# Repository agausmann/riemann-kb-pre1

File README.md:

# Riemann

A pseudo-split 60% ortholinear keyboard.

## Main Features

- 60 keys in a 5x12 grid

- Supports MX-style switches

- Per-key RGB

- Hot-swappable

- QMK support (TODO)

## Design

- Designed with the features that I want, with no compromises.

- Designed to be factory-assembled, _not_ hand-soldered (I want to be able to rely on this, and I don't trust my soldering skills _that_ much).

- Microcontroller is selected to be compatible with the [Rust] programming 
language (unfortunately it does not have good support for AVR)

- PRETTY COLORS (RGB LEDs are based on the APA102 IC for that sweet, sweet
dynamic range, compared to WS2812)

[Rust]: https://rust-lang.org

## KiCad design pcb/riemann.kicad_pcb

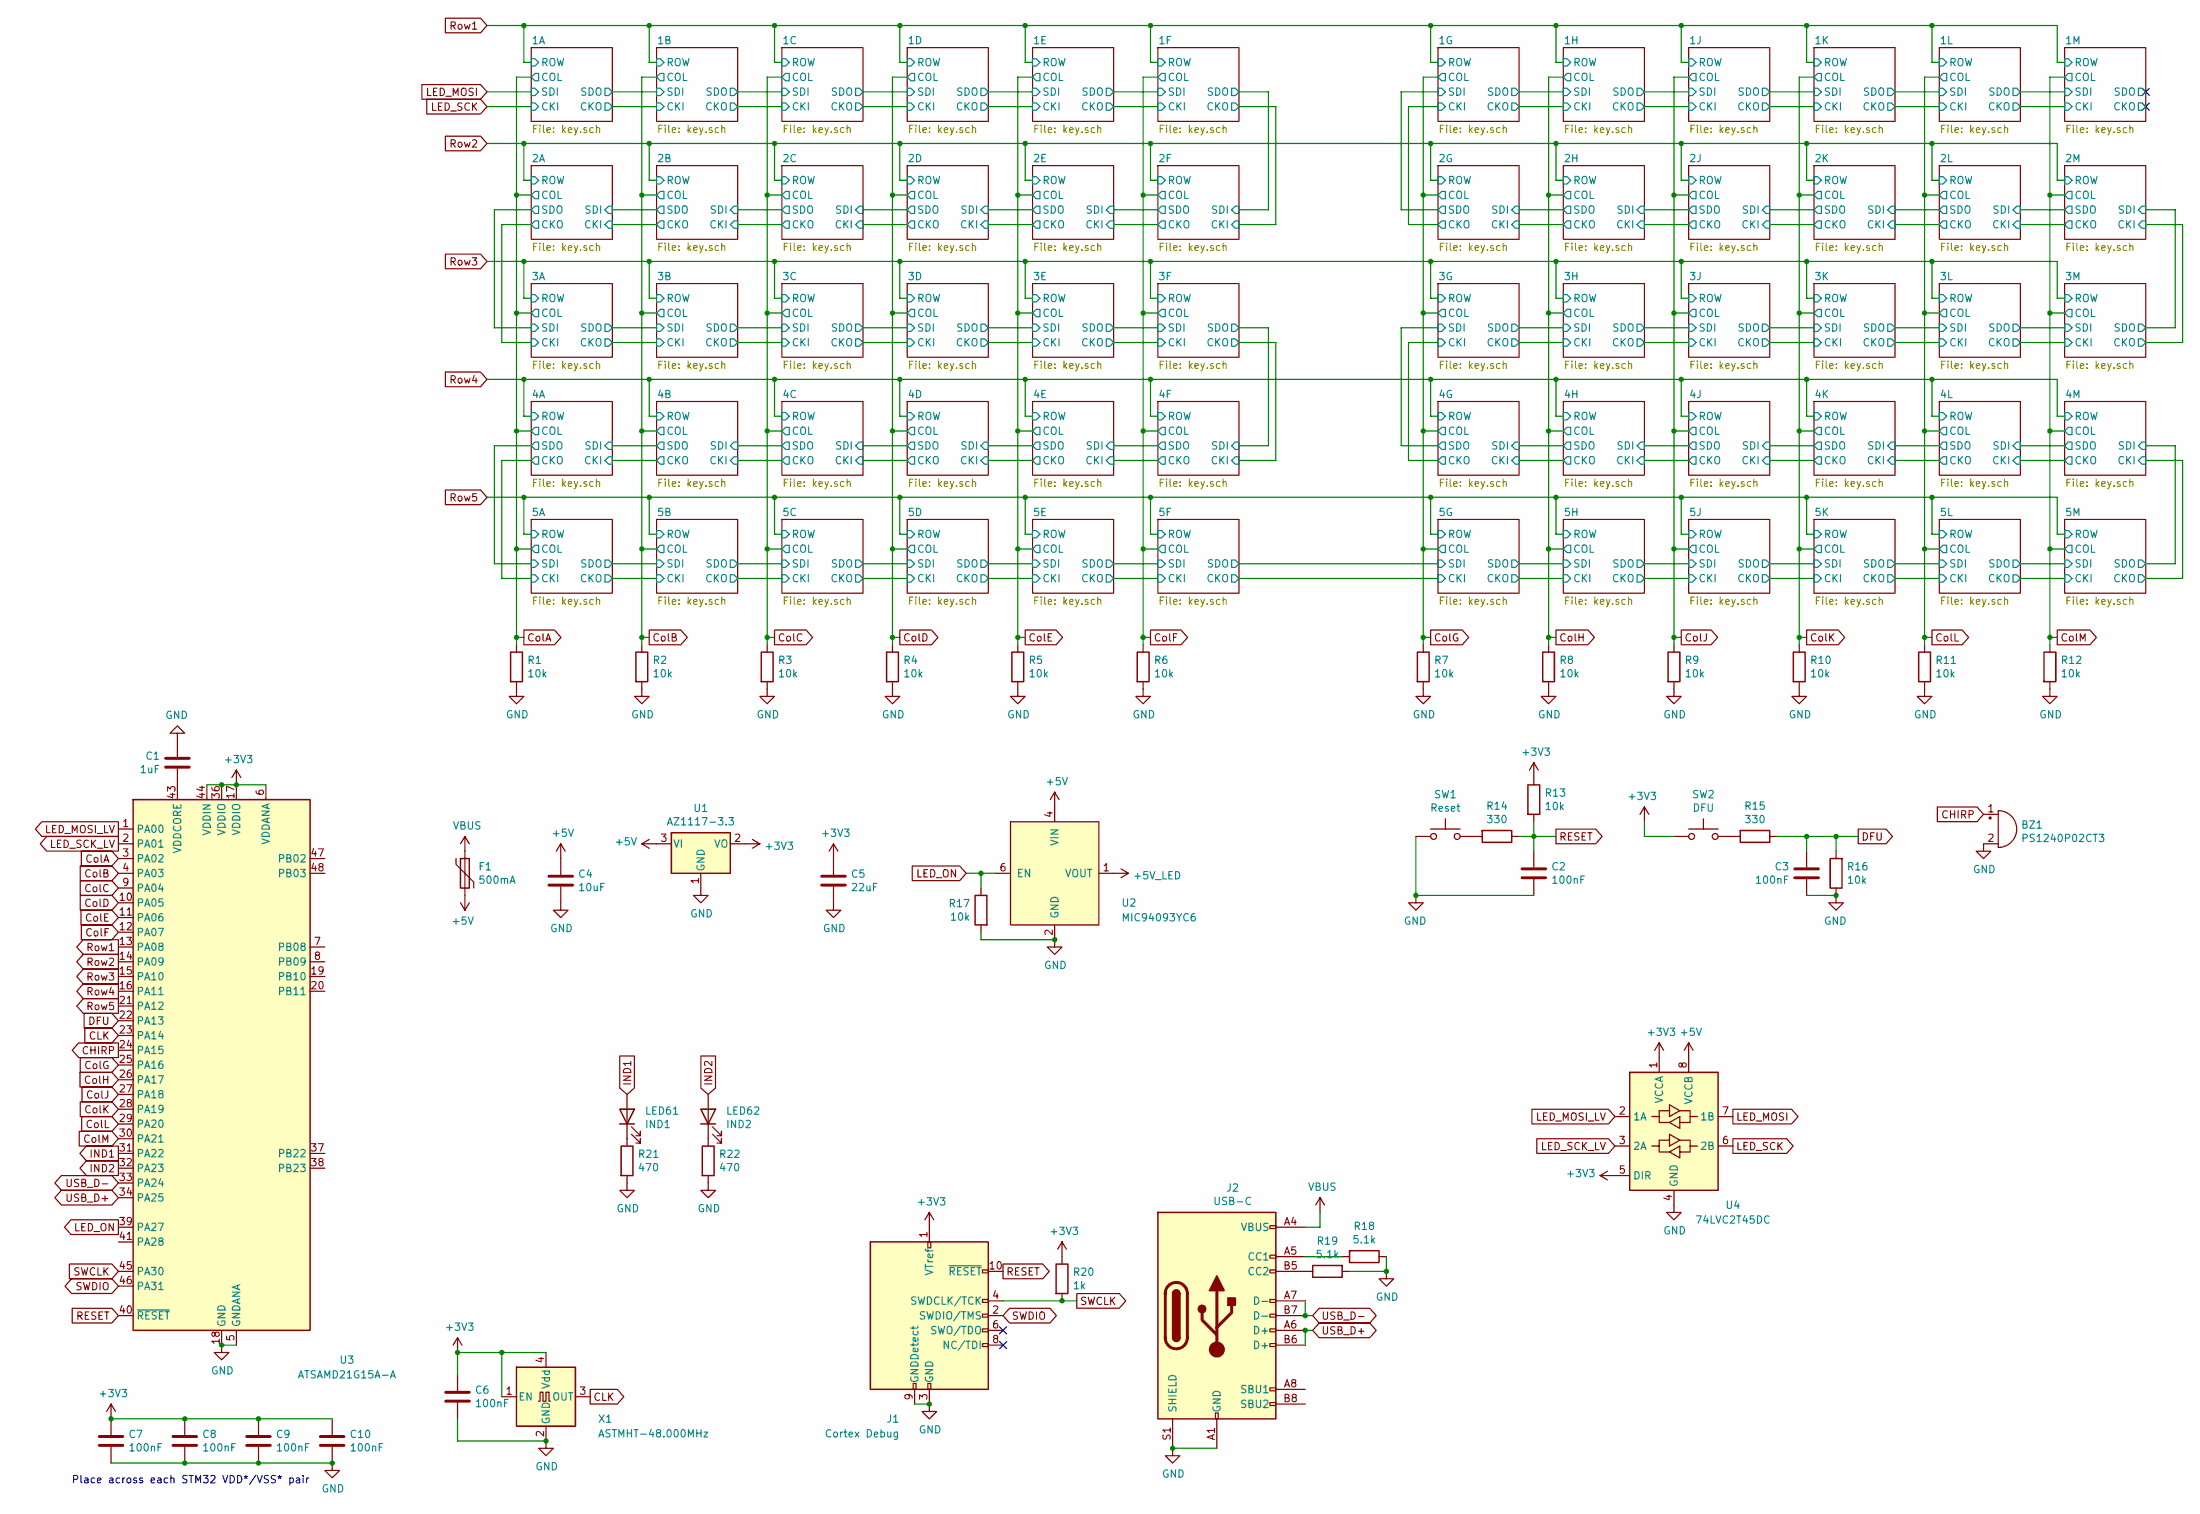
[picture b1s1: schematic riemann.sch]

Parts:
BZ1: PS1240P02CT3; Buzzer_TDK_PS1240P02BT_D12.2mm_H6.5mm; Mfr. Part PS1240P02CT3; Digikey 445-5229-1-ND
C1: 1uF; C_0402_1005Metric; Mfr. Part CL05A105MQ5NNNC; Digikey 1276-1235-1-ND
C2, C3: 100nF; C_0603_1608Metric; Mfr. Part CL10B104KA8NNNC; Digikey 1276-1006-1-ND
C4: 10uF; C_0805_2012Metric; Mfr. Part CL21A106KOFNNNE; Digikey 1276-2893-1-ND
C5: 22uF; C_0805_2012Metric; Mfr. Part CL21A226MOCLRNC; Digikey 1276-6780-1-ND
C6, C7, C8, C9, C10: 100nF; C_0402_1005Metric; Mfr. Part CL05A104KA5NNNC; Digikey 1276-1043-1-ND
F1: 500mA; Fuse_0805_2012Metric_Castellated; Mfr. Part 0ZCK0050FF2E; Digikey 507-1813-1-ND
J1: Cortex Debug; Samtec_FTSH-105_2x05_P1.27mm_Keyed_Vertical; Mfr. Part FTSH-105-01-L-DV-K-A-P-TR; Digikey SAM13163CT-ND
J2: USB-C; USB_C_Receptacle_GCT_USB4105; Mfr. Part USB4105-GF-A; Digikey 2073-USB4105-GF-ACT-ND
LED61: IND1; LED_0603_1608Metric; Mfr. Part 150060AS75000; Digikey 732-150060AS75000CT-ND
LED62: IND2; LED_0603_1608Metric; Mfr. Part 150060BS75000; Digikey 732-4966-1-ND
R1, R2, R3, R4, R5, R6, R7, R8, R9, R10, R11, R12, R13, R16, R17: 10k; R_0603_1608Metric; Mfr. Part RMCF0603FT10K0; Digikey RMCF0603FT10K0CT-ND
R14, R15: 330; R_0603_1608Metric; Mfr. Part RMCF0603FT330R; Digikey RMCF0603FT330RCT-ND
R18, R19: 5.1k; R_0603_1608Metric; Mfr. Part RMCF0603FT5K10; Digikey RMCF0603FT5K10CT-ND
R20: 1k; R_0402_1005Metric; Mfr. Part RMCF0402FT1K00; Digikey RMCF0402FT1K00CT-ND
R21, R22: 470; R_0603_1608Metric
SW1: Reset; SW_Push_1P1T_NO_6x6mm_H9.5mm; Mfr. Part PTS645SL43SMTR92 LFS; Digikey CKN10880CT-ND
SW2: DFU; SW_Push_1P1T_NO_6x6mm_H9.5mm; Mfr. Part PTS645SL43SMTR92 LFS; Digikey CKN10880CT-ND
U1: AZ1117-3.3; SOT-223-3_TabPin2; Mfr. Part AZ1117IH-3.3TRG1; Digikey AZ1117IH-3.3TRG1DICT-ND
U2: MIC94093YC6; SOT-363_SC-70-6; Mfr. Part MIC94093YC6-TR; Digikey 576-3490-1-ND
U3: ATSAMD21G15A-A; TQFP-48_7x7mm_P0.5mm; Mfr. Part ATSAMD21G18A-AFT; Digikey ATSAMD21G18A-AFTCT-ND
U4: 74LVC2T45DC; VSSOP-8_2.3x2mm_P0.5mm; Mfr. Part 74LVCH2T45DC,125; Digikey 1727-4596-1-ND
X1: ASTMHT-48.000MHz; Oscillator_SMD_Abracon_ASE-4Pin_3.2x2.5mm; Mfr. Part ASTMHTE-48.000MHZ-AJ-E-T; Digikey 535-13269-1-ND

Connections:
+3V3: C5.1, C6.1, C7.1, C8.1, C9.1, C10.1, J1.1 (VTref), R13.1, R20.1, SW2.2, U1.2 (VO), U3.6 (VDDANA), U3.17 (VDDIO), U3.36 (VDDIO), U3.44 (VDDIN), U4.1 (VCCA), U4.5 (DIR), X1.1 (EN), X1.4 (Vdd)
+5V: C4.1, F1.2, U1.3 (VI), U2.4 (VIN), U4.8 (VCCB)
+5V_LED: U2.1 (VOUT); also elsewhere on the board
CHIRP: BZ1.1 (-), U3.24 (PA15)
CLK: U3.23 (PA14), X1.3 (OUT)
ColA: R1.1, U3.3 (PA02); also elsewhere on the board
ColB: R2.1, U3.4 (PA03); also elsewhere on the board
ColC: R3.1, U3.9 (PA04); also elsewhere on the board
ColD: R4.1, U3.10 (PA05); also elsewhere on the board
ColE: R5.1, U3.11 (PA06); also elsewhere on the board
ColF: R6.1, U3.12 (PA07); also elsewhere on the board
ColG: R7.1, U3.25 (PA16); also elsewhere on the board
ColH: R8.1, U3.26 (PA17); also elsewhere on the board
ColJ: R9.1, U3.27 (PA18); also elsewhere on the board
ColK: R10.1, U3.28 (PA19); also elsewhere on the board
ColL: R11.1, U3.29 (PA20); also elsewhere on the board
ColM: R12.1, U3.30 (PA21); also elsewhere on the board
DFU: C3.1, R15.1, R16.2, U3.22 (PA13)
GND: BZ1.2 (+), C1.2, C2.2, C3.2, C4.2, C5.2, C6.2, C7.2, C8.2, C9.2, C10.2, J1.3 (GND), J1.5 (GND), J1.9 (GNDDetect), J2.A1 (GND), J2.A12 (GND), J2.B1 (GND), J2.B12 (GND), J2.S1 (SHIELD), R1.2, R2.2, R3.2, R4.2, R5.2, R6.2, R7.2, R8.2, R9.2, R10.2, R11.2, R12.2, R16.1, R17.2, R18.1, R19.2, R21.2, R22.2, SW1.1, U1.1 (GND), U2.2 (GND), U2.5 (GND), U3.5 (GNDANA), U3.18 (GND), U3.35 (GND), U3.42 (GND), U4.4 (GND), X1.2 (GND); also elsewhere on the board
IND1: LED61.2 (A), U3.31 (PA22)
IND2: LED62.2 (A), U3.32 (PA23)
LED_MOSI: U4.7 (1B); also elsewhere on the board
LED_MOSI_LV: U3.1 (PA00), U4.2 (1A)
LED_ON: R17.1, U2.6 (EN), U3.39 (PA27)
LED_SCK: U4.6 (2B); also elsewhere on the board
LED_SCK_LV: U3.2 (PA01), U4.3 (2A)
unnamed: C1.1, U3.43 (VDDCORE)
unnamed: J2.A5 (CC1), R18.2
unnamed: J2.B5 (CC2), R19.1
unnamed: LED61.1 (K), R21.1
unnamed: LED62.1 (K), R22.1
unnamed: R14.2, SW1.2
unnamed: R15.2, SW2.1
RESET: C2.1, J1.10 (~RESET~), R13.2, R14.1, U3.40 (~RESET)
Row1: U3.13 (PA08); also elsewhere on the board
Row2: U3.14 (PA09); also elsewhere on the board
Row3: U3.15 (PA10); also elsewhere on the board
Row4: U3.16 (PA11); also elsewhere on the board
Row5: U3.21 (PA12); also elsewhere on the board
SWCLK: J1.4 (SWDCLK/TCK), R20.2, U3.45 (PA30)
SWDIO: J1.2 (SWDIO/TMS), U3.46 (PA31)
USB_D+: J2.A6 (D+), J2.B6 (D+), U3.34 (PA25)
USB_D-: J2.A7 (D-), J2.B7 (D-), U3.33 (PA24)
VBUS: F1.1, J2.A4 (VBUS), J2.A9 (VBUS), J2.B4 (VBUS), J2.B9 (VBUS)

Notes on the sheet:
Place across each STM32 VDD*/VSS* pair

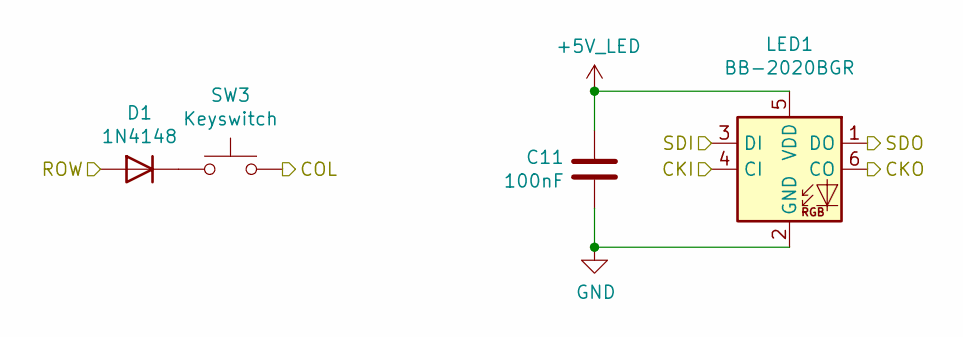
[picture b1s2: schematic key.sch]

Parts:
C11: 100nF; C_0402_1005Metric; Mfr. Part CL05A104KA5NNNC; Digikey 1276-1043-1-ND
D1: 1N4148; D_SOD-123; Mfr. Part 1N4148WSTR; Digikey 1655-1359-1-ND
LED1: BB-2020BGR; LED-BB-2020BGR; Mfr. Part BB-2020BGR-TRB; Digikey 2007-BB-2020BGR-TRBCT-ND
SW3: Keyswitch; SW_GateronRGB_KailhSocket_1.00u_PCB; Mfr. Part CPG151101S11

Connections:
+5V_LED: C11.2, LED1.5 (VDD); also elsewhere on the board
/1B/CKI: LED1.6 (CO); also elsewhere on the board
/1B/SDI: LED1.1 (DO); also elsewhere on the board
ColA: SW3.2; also elsewhere on the board
GND: C11.1, LED1.2 (GND); also elsewhere on the board
LED_MOSI: LED1.3 (DI); also elsewhere on the board
LED_SCK: LED1.4 (CI); also elsewhere on the board
unnamed: D1.1 (K), SW3.1
Row1: D1.2 (A); also elsewhere on the board

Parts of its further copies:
C12, C13, C14, C15, C16, C17, C18, C19, C20, C21, C22, C23, C24, C25, C26, C27, C28, C29, C30, C31, C32, C33, C34, C35, C36, C37, C38, C39, C40, C41, C42, C43, C44, C45, C46, C47, C48, C49, C50, C51, C52, C53, C54, C55, C56, C57, C58, C59, C60, C61, C62, C63, C64, C65, C66, C67, C68, C69, C70: 100nF; C_0402_1005Metric; Mfr. Part CL05A104KA5NNNC; Digikey 1276-1043-1-ND
D2, D3, D4, D5, D6, D7, D8, D9, D10, D11, D12, D13, D14, D15, D16, D17, D18, D19, D20, D21, D22, D23, D24, D25, D26, D27, D28, D29, D30, D31, D32, D33, D34, D35, D36, D37, D38, D39, D40, D41, D42, D43, D44, D45, D46, D47, D48, D49, D50, D51, D52, D53, D54, D55, D56, D57, D58, D59, D60: 1N4148; D_SOD-123; Mfr. Part 1N4148WSTR; Digikey 1655-1359-1-ND
LED2, LED3, LED4, LED5, LED6, LED7, LED8, LED9, LED10, LED11, LED12, LED13, LED14, LED15, LED16, LED17, LED18, LED19, LED20, LED21, LED22, LED23, LED24, LED25, LED26, LED27, LED28, LED29, LED30, LED31, LED32, LED33, LED34, LED35, LED36, LED37, LED38, LED39, LED40, LED41, LED42, LED43, LED44, LED45, LED46, LED47, LED48, LED49, LED50, LED51, LED52, LED53, LED54, LED55, LED56, LED57, LED58, LED59, LED60: BB-2020BGR; LED-BB-2020BGR; Mfr. Part BB-2020BGR-TRB; Digikey 2007-BB-2020BGR-TRBCT-ND
SW4, SW5, SW6, SW7, SW8, SW9, SW10, SW11, SW12, SW13, SW14, SW15, SW16, SW17, SW18, SW19, SW20, SW21, SW22, SW23, SW24, SW25, SW26, SW27, SW28, SW29, SW30, SW31, SW32, SW33, SW34, SW35, SW36, SW37, SW38, SW39, SW40, SW41, SW42, SW43, SW44, SW45, SW46, SW47, SW48, SW49, SW50, SW51, SW52, SW53, SW54, SW55, SW56, SW57, SW58, SW59, SW60, SW61, SW62: Keyswitch; SW_GateronRGB_KailhSocket_1.00u_PCB; Mfr. Part CPG151101S11

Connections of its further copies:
+5V_LED: C12.2, C13.2, C14.2, C15.2, C16.2, C17.2, C18.2, C19.2, C20.2, C21.2, C22.2, C23.2, C24.2, C25.2, C26.2, C27.2, C28.2, C29.2, C30.2, C31.2, C32.2, C33.2, C34.2, C35.2, C36.2, C37.2, C38.2, C39.2, C40.2, C41.2, C42.2, C43.2, C44.2, C45.2, C46.2, C47.2, C48.2, C49.2, C50.2, C51.2, C52.2, C53.2, C54.2, C55.2, C56.2, C57.2, C58.2, C59.2, C60.2, C61.2, C62.2, C63.2, C64.2, C65.2, C66.2, C67.2, C68.2, C69.2, C70.2, LED2.5 (VDD), LED3.5 (VDD), LED4.5 (VDD), LED5.5 (VDD), LED6.5 (VDD), LED7.5 (VDD), LED8.5 (VDD), LED9.5 (VDD), LED10.5 (VDD), LED11.5 (VDD), LED12.5 (VDD), LED13.5 (VDD), LED14.5 (VDD), LED15.5 (VDD), LED16.5 (VDD), LED17.5 (VDD), LED18.5 (VDD), LED19.5 (VDD), LED20.5 (VDD), LED21.5 (VDD), LED22.5 (VDD), LED23.5 (VDD), LED24.5 (VDD), LED25.5 (VDD), LED26.5 (VDD), LED27.5 (VDD), LED28.5 (VDD), LED29.5 (VDD), LED30.5 (VDD), LED31.5 (VDD), LED32.5 (VDD), LED33.5 (VDD), LED34.5 (VDD), LED35.5 (VDD), LED36.5 (VDD), LED37.5 (VDD), LED38.5 (VDD), LED39.5 (VDD), LED40.5 (VDD), LED41.5 (VDD), LED42.5 (VDD), LED43.5 (VDD), LED44.5 (VDD), LED45.5 (VDD), LED46.5 (VDD), LED47.5 (VDD), LED48.5 (VDD), LED49.5 (VDD), LED50.5 (VDD), LED51.5 (VDD), LED52.5 (VDD), LED53.5 (VDD), LED54.5 (VDD), LED55.5 (VDD), LED56.5 (VDD), LED57.5 (VDD), LED58.5 (VDD), LED59.5 (VDD), LED60.5 (VDD); also elsewhere on the board
/1B/CKI: LED2.4 (CI); also elsewhere on the board
/1B/SDI: LED2.3 (DI); also elsewhere on the board
/1C/CKI: LED2.6 (CO), LED3.4 (CI)
/1C/SDI: LED2.1 (DO), LED3.3 (DI)
/1D/CKI: LED3.6 (CO), LED4.4 (CI)
/1D/SDI: LED3.1 (DO), LED4.3 (DI)
/1E/CKI: LED4.6 (CO), LED5.4 (CI)
/1E/SDI: LED4.1 (DO), LED5.3 (DI)
/1F/CKI: LED5.6 (CO), LED6.4 (CI)
/1F/SDI: LED5.1 (DO), LED6.3 (DI)
/1G/CKI: LED7.4 (CI), LED19.6 (CO)
/1G/SDI: LED7.3 (DI), LED19.1 (DO)
/1H/CKI: LED7.6 (CO), LED8.4 (CI)
/1H/SDI: LED7.1 (DO), LED8.3 (DI)
/1J/CKI: LED8.6 (CO), LED9.4 (CI)
/1J/SDI: LED8.1 (DO), LED9.3 (DI)
/1K/CKI: LED9.6 (CO), LED10.4 (CI)
/1K/SDI: LED9.1 (DO), LED10.3 (DI)
/1L/CKI: LED10.6 (CO), LED11.4 (CI)
/1L/SDI: LED10.1 (DO), LED11.3 (DI)
/1M/CKI: LED11.6 (CO), LED12.4 (CI)
/1M/CKO: LED12.6 (CO)
/1M/SDI: LED11.1 (DO), LED12.3 (DI)
/1M/SDO: LED12.1 (DO)
/2A/CKI: LED13.4 (CI), LED14.6 (CO)
/2A/SDI: LED13.3 (DI), LED14.1 (DO)
/2B/CKI: LED14.4 (CI), LED15.6 (CO)
/2B/SDI: LED14.3 (DI), LED15.1 (DO)
/2C/CKI: LED15.4 (CI), LED16.6 (CO)
/2C/SDI: LED15.3 (DI), LED16.1 (DO)
/2D/CKI: LED16.4 (CI), LED17.6 (CO)
/2D/SDI: LED16.3 (DI), LED17.1 (DO)
/2E/CKI: LED17.4 (CI), LED18.6 (CO)
/2E/SDI: LED17.3 (DI), LED18.1 (DO)
/2F/CKI: LED6.6 (CO), LED18.4 (CI)
/2F/SDI: LED6.1 (DO), LED18.3 (DI)
/2G/CKI: LED19.4 (CI), LED20.6 (CO)
/2G/SDI: LED19.3 (DI), LED20.1 (DO)
/2H/CKI: LED20.4 (CI), LED21.6 (CO)
/2H/SDI: LED20.3 (DI), LED21.1 (DO)
/2J/CKI: LED21.4 (CI), LED22.6 (CO)
/2J/SDI: LED21.3 (DI), LED22.1 (DO)
/2K/CKI: LED22.4 (CI), LED23.6 (CO)
/2K/SDI: LED22.3 (DI), LED23.1 (DO)
/2L/CKI: LED23.4 (CI), LED24.6 (CO)
/2L/SDI: LED23.3 (DI), LED24.1 (DO)
/2M/CKI: LED24.4 (CI), LED36.6 (CO)
/2M/SDI: LED24.3 (DI), LED36.1 (DO)
/3A/CKI: LED13.6 (CO), LED25.4 (CI)
/3A/SDI: LED13.1 (DO), LED25.3 (DI)
/3B/CKI: LED25.6 (CO), LED26.4 (CI)
/3B/SDI: LED25.1 (DO), LED26.3 (DI)
/3C/CKI: LED26.6 (CO), LED27.4 (CI)
/3C/SDI: LED26.1 (DO), LED27.3 (DI)
/3D/CKI: LED27.6 (CO), LED28.4 (CI)
/3D/SDI: LED27.1 (DO), LED28.3 (DI)
/3E/CKI: LED28.6 (CO), LED29.4 (CI)
/3E/SDI: LED28.1 (DO), LED29.3 (DI)
/3F/CKI: LED29.6 (CO), LED30.4 (CI)
/3F/SDI: LED29.1 (DO), LED30.3 (DI)
/3G/CKI: LED31.4 (CI), LED43.6 (CO)
/3G/SDI: LED31.3 (DI), LED43.1 (DO)
/3H/CKI: LED31.6 (CO), LED32.4 (CI)
/3H/SDI: LED31.1 (DO), LED32.3 (DI)
/3J/CKI: LED32.6 (CO), LED33.4 (CI)
/3J/SDI: LED32.1 (DO), LED33.3 (DI)
/3K/CKI: LED33.6 (CO), LED34.4 (CI)
/3K/SDI: LED33.1 (DO), LED34.3 (DI)
/3L/CKI: LED34.6 (CO), LED35.4 (CI)
/3L/SDI: LED34.1 (DO), LED35.3 (DI)
/3M/CKI: LED35.6 (CO), LED36.4 (CI)
/3M/SDI: LED35.1 (DO), LED36.3 (DI)
/4A/CKI: LED37.4 (CI), LED38.6 (CO)
/4A/SDI: LED37.3 (DI), LED38.1 (DO)
/4B/CKI: LED38.4 (CI), LED39.6 (CO)
/4B/SDI: LED38.3 (DI), LED39.1 (DO)
/4C/CKI: LED39.4 (CI), LED40.6 (CO)
/4C/SDI: LED39.3 (DI), LED40.1 (DO)
/4D/CKI: LED40.4 (CI), LED41.6 (CO)
/4D/SDI: LED40.3 (DI), LED41.1 (DO)
/4E/CKI: LED41.4 (CI), LED42.6 (CO)
/4E/SDI: LED41.3 (DI), LED42.1 (DO)
/4F/CKI: LED30.6 (CO), LED42.4 (CI)
/4F/SDI: LED30.1 (DO), LED42.3 (DI)
/4G/CKI: LED43.4 (CI), LED44.6 (CO)
/4G/SDI: LED43.3 (DI), LED44.1 (DO)
/4H/CKI: LED44.4 (CI), LED45.6 (CO)
/4H/SDI: LED44.3 (DI), LED45.1 (DO)
/4J/CKI: LED45.4 (CI), LED46.6 (CO)
/4J/SDI: LED45.3 (DI), LED46.1 (DO)
/4K/CKI: LED46.4 (CI), LED47.6 (CO)
/4K/SDI: LED46.3 (DI), LED47.1 (DO)
/4L/CKI: LED47.4 (CI), LED48.6 (CO)
/4L/SDI: LED47.3 (DI), LED48.1 (DO)
/4M/CKI: LED48.4 (CI), LED60.6 (CO)
/4M/SDI: LED48.3 (DI), LED60.1 (DO)
/5A/CKI: LED37.6 (CO), LED49.4 (CI)
/5A/SDI: LED37.1 (DO), LED49.3 (DI)
/5B/CKI: LED49.6 (CO), LED50.4 (CI)
/5B/SDI: LED49.1 (DO), LED50.3 (DI)
/5C/CKI: LED50.6 (CO), LED51.4 (CI)
/5C/SDI: LED50.1 (DO), LED51.3 (DI)
/5D/CKI: LED51.6 (CO), LED52.4 (CI)
/5D/SDI: LED51.1 (DO), LED52.3 (DI)
/5E/CKI: LED52.6 (CO), LED53.4 (CI)
/5E/SDI: LED52.1 (DO), LED53.3 (DI)
/5F/CKI: LED53.6 (CO), LED54.4 (CI)
/5F/SDI: LED53.1 (DO), LED54.3 (DI)
/5G/CKI: LED54.6 (CO), LED55.4 (CI)
/5G/SDI: LED54.1 (DO), LED55.3 (DI)
/5H/CKI: LED55.6 (CO), LED56.4 (CI)
/5H/SDI: LED55.1 (DO), LED56.3 (DI)
/5J/CKI: LED56.6 (CO), LED57.4 (CI)
/5J/SDI: LED56.1 (DO), LED57.3 (DI)
/5K/CKI: LED57.6 (CO), LED58.4 (CI)
/5K/SDI: LED57.1 (DO), LED58.3 (DI)
/5L/CKI: LED58.6 (CO), LED59.4 (CI)
/5L/SDI: LED58.1 (DO), LED59.3 (DI)
/5M/CKI: LED59.6 (CO), LED60.4 (CI)
/5M/SDI: LED59.1 (DO), LED60.3 (DI)
ColA: SW15.2, SW27.2, SW39.2, SW51.2; also elsewhere on the board
ColB: SW4.2, SW16.2, SW28.2, SW40.2, SW52.2; also elsewhere on the board
ColC: SW5.2, SW17.2, SW29.2, SW41.2, SW53.2; also elsewhere on the board
ColD: SW6.2, SW18.2, SW30.2, SW42.2, SW54.2; also elsewhere on the board
ColE: SW7.2, SW19.2, SW31.2, SW43.2, SW55.2; also elsewhere on the board
ColF: SW8.2, SW20.2, SW32.2, SW44.2, SW56.2; also elsewhere on the board
ColG: SW9.2, SW21.2, SW33.2, SW45.2, SW57.2; also elsewhere on the board
ColH: SW10.2, SW22.2, SW34.2, SW46.2, SW58.2; also elsewhere on the board
ColJ: SW11.2, SW23.2, SW35.2, SW47.2, SW59.2; also elsewhere on the board
ColK: SW12.2, SW24.2, SW36.2, SW48.2, SW60.2; also elsewhere on the board
ColL: SW13.2, SW25.2, SW37.2, SW49.2, SW61.2; also elsewhere on the board
ColM: SW14.2, SW26.2, SW38.2, SW50.2, SW62.2; also elsewhere on the board
GND: C12.1, C13.1, C14.1, C15.1, C16.1, C17.1, C18.1, C19.1, C20.1, C21.1, C22.1, C23.1, C24.1, C25.1, C26.1, C27.1, C28.1, C29.1, C30.1, C31.1, C32.1, C33.1, C34.1, C35.1, C36.1, C37.1, C38.1, C39.1, C40.1, C41.1, C42.1, C43.1, C44.1, C45.1, C46.1, C47.1, C48.1, C49.1, C50.1, C51.1, C52.1, C53.1, C54.1, C55.1, C56.1, C57.1, C58.1, C59.1, C60.1, C61.1, C62.1, C63.1, C64.1, C65.1, C66.1, C67.1, C68.1, C69.1, C70.1, LED2.2 (GND), LED3.2 (GND), LED4.2 (GND), LED5.2 (GND), LED6.2 (GND), LED7.2 (GND), LED8.2 (GND), LED9.2 (GND), LED10.2 (GND), LED11.2 (GND), LED12.2 (GND), LED13.2 (GND), LED14.2 (GND), LED15.2 (GND), LED16.2 (GND), LED17.2 (GND), LED18.2 (GND), LED19.2 (GND), LED20.2 (GND), LED21.2 (GND), LED22.2 (GND), LED23.2 (GND), LED24.2 (GND), LED25.2 (GND), LED26.2 (GND), LED27.2 (GND), LED28.2 (GND), LED29.2 (GND), LED30.2 (GND), LED31.2 (GND), LED32.2 (GND), LED33.2 (GND), LED34.2 (GND), LED35.2 (GND), LED36.2 (GND), LED37.2 (GND), LED38.2 (GND), LED39.2 (GND), LED40.2 (GND), LED41.2 (GND), LED42.2 (GND), LED43.2 (GND), LED44.2 (GND), LED45.2 (GND), LED46.2 (GND), LED47.2 (GND), LED48.2 (GND), LED49.2 (GND), LED50.2 (GND), LED51.2 (GND), LED52.2 (GND), LED53.2 (GND), LED54.2 (GND), LED55.2 (GND), LED56.2 (GND), LED57.2 (GND), LED58.2 (GND), LED59.2 (GND), LED60.2 (GND); also elsewhere on the board
unnamed: D2.1 (K), SW4.1
unnamed: D3.1 (K), SW5.1
unnamed: D4.1 (K), SW6.1
unnamed: D5.1 (K), SW7.1
unnamed: D6.1 (K), SW8.1
unnamed: D7.1 (K), SW9.1
unnamed: D8.1 (K), SW10.1
unnamed: D9.1 (K), SW11.1
unnamed: D10.1 (K), SW12.1
unnamed: D11.1 (K), SW13.1
unnamed: D12.1 (K), SW14.1
unnamed: D13.1 (K), SW15.1
unnamed: D14.1 (K), SW16.1
unnamed: D15.1 (K), SW17.1
unnamed: D16.1 (K), SW18.1
unnamed: D17.1 (K), SW19.1
unnamed: D18.1 (K), SW20.1
unnamed: D19.1 (K), SW21.1
unnamed: D20.1 (K), SW22.1
unnamed: D21.1 (K), SW23.1
unnamed: D22.1 (K), SW24.1
unnamed: D23.1 (K), SW25.1
unnamed: D24.1 (K), SW26.1
unnamed: D25.1 (K), SW27.1
unnamed: D26.1 (K), SW28.1
unnamed: D27.1 (K), SW29.1
unnamed: D28.1 (K), SW30.1
unnamed: D29.1 (K), SW31.1
unnamed: D30.1 (K), SW32.1
unnamed: D31.1 (K), SW33.1
unnamed: D32.1 (K), SW34.1
unnamed: D33.1 (K), SW35.1
unnamed: D34.1 (K), SW36.1
unnamed: D35.1 (K), SW37.1
unnamed: D36.1 (K), SW38.1
unnamed: D37.1 (K), SW39.1
unnamed: D38.1 (K), SW40.1
unnamed: D39.1 (K), SW41.1
unnamed: D40.1 (K), SW42.1
unnamed: D41.1 (K), SW43.1
unnamed: D42.1 (K), SW44.1
unnamed: D43.1 (K), SW45.1
unnamed: D44.1 (K), SW46.1
unnamed: D45.1 (K), SW47.1
unnamed: D46.1 (K), SW48.1
unnamed: D47.1 (K), SW49.1
unnamed: D48.1 (K), SW50.1
unnamed: D49.1 (K), SW51.1
unnamed: D50.1 (K), SW52.1
unnamed: D51.1 (K), SW53.1
unnamed: D52.1 (K), SW54.1
unnamed: D53.1 (K), SW55.1
unnamed: D54.1 (K), SW56.1
unnamed: D55.1 (K), SW57.1
unnamed: D56.1 (K), SW58.1
unnamed: D57.1 (K), SW59.1
unnamed: D58.1 (K), SW60.1
unnamed: D59.1 (K), SW61.1
unnamed: D60.1 (K), SW62.1
Row1: D2.2 (A), D3.2 (A), D4.2 (A), D5.2 (A), D6.2 (A), D7.2 (A), D8.2 (A), D9.2 (A), D10.2 (A), D11.2 (A), D12.2 (A); also elsewhere on the board
Row2: D13.2 (A), D14.2 (A), D15.2 (A), D16.2 (A), D17.2 (A), D18.2 (A), D19.2 (A), D20.2 (A), D21.2 (A), D22.2 (A), D23.2 (A), D24.2 (A); also elsewhere on the board
Row3: D25.2 (A), D26.2 (A), D27.2 (A), D28.2 (A), D29.2 (A), D30.2 (A), D31.2 (A), D32.2 (A), D33.2 (A), D34.2 (A), D35.2 (A), D36.2 (A); also elsewhere on the board
Row4: D37.2 (A), D38.2 (A), D39.2 (A), D40.2 (A), D41.2 (A), D42.2 (A), D43.2 (A), D44.2 (A), D45.2 (A), D46.2 (A), D47.2 (A), D48.2 (A); also elsewhere on the board
Row5: D49.2 (A), D50.2 (A), D51.2 (A), D52.2 (A), D53.2 (A), D54.2 (A), D55.2 (A), D56.2 (A), D57.2 (A), D58.2 (A), D59.2 (A), D60.2 (A); also elsewhere on the board

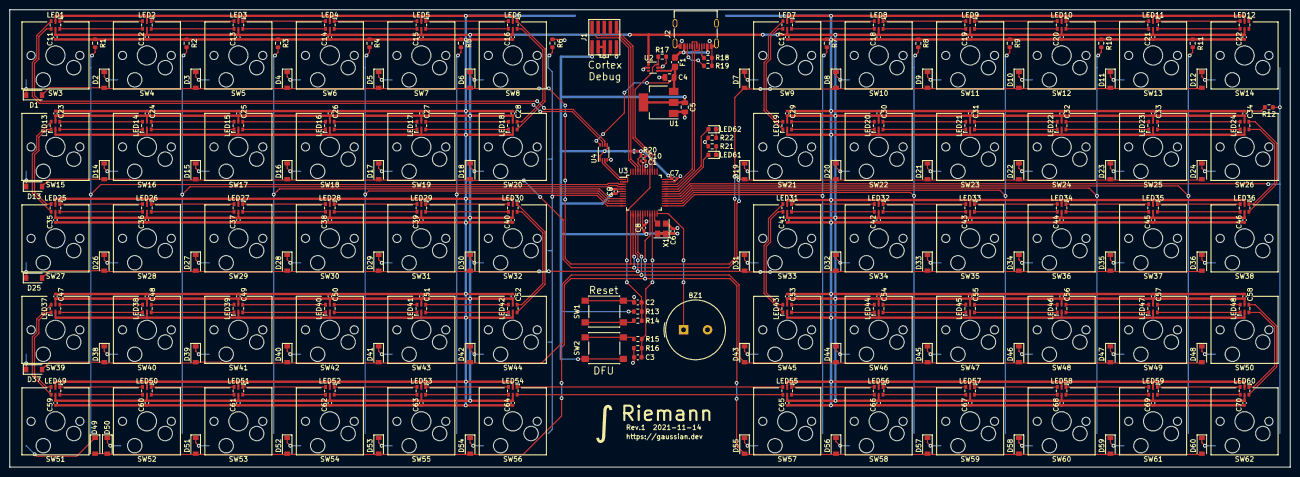
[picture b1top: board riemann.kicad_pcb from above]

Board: 2 copper layers, 266.7 x 95.2 mm, 285 parts (0 on the bottom side), 222 nets.

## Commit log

2021-11-14 Initial design
2021-11-14 Add README, LICENSE
2021-11-14 Move PCB design files into a subfolder
2021-11-15 Add branding to PCB
2021-11-15 Add PCB design screenshot to README
